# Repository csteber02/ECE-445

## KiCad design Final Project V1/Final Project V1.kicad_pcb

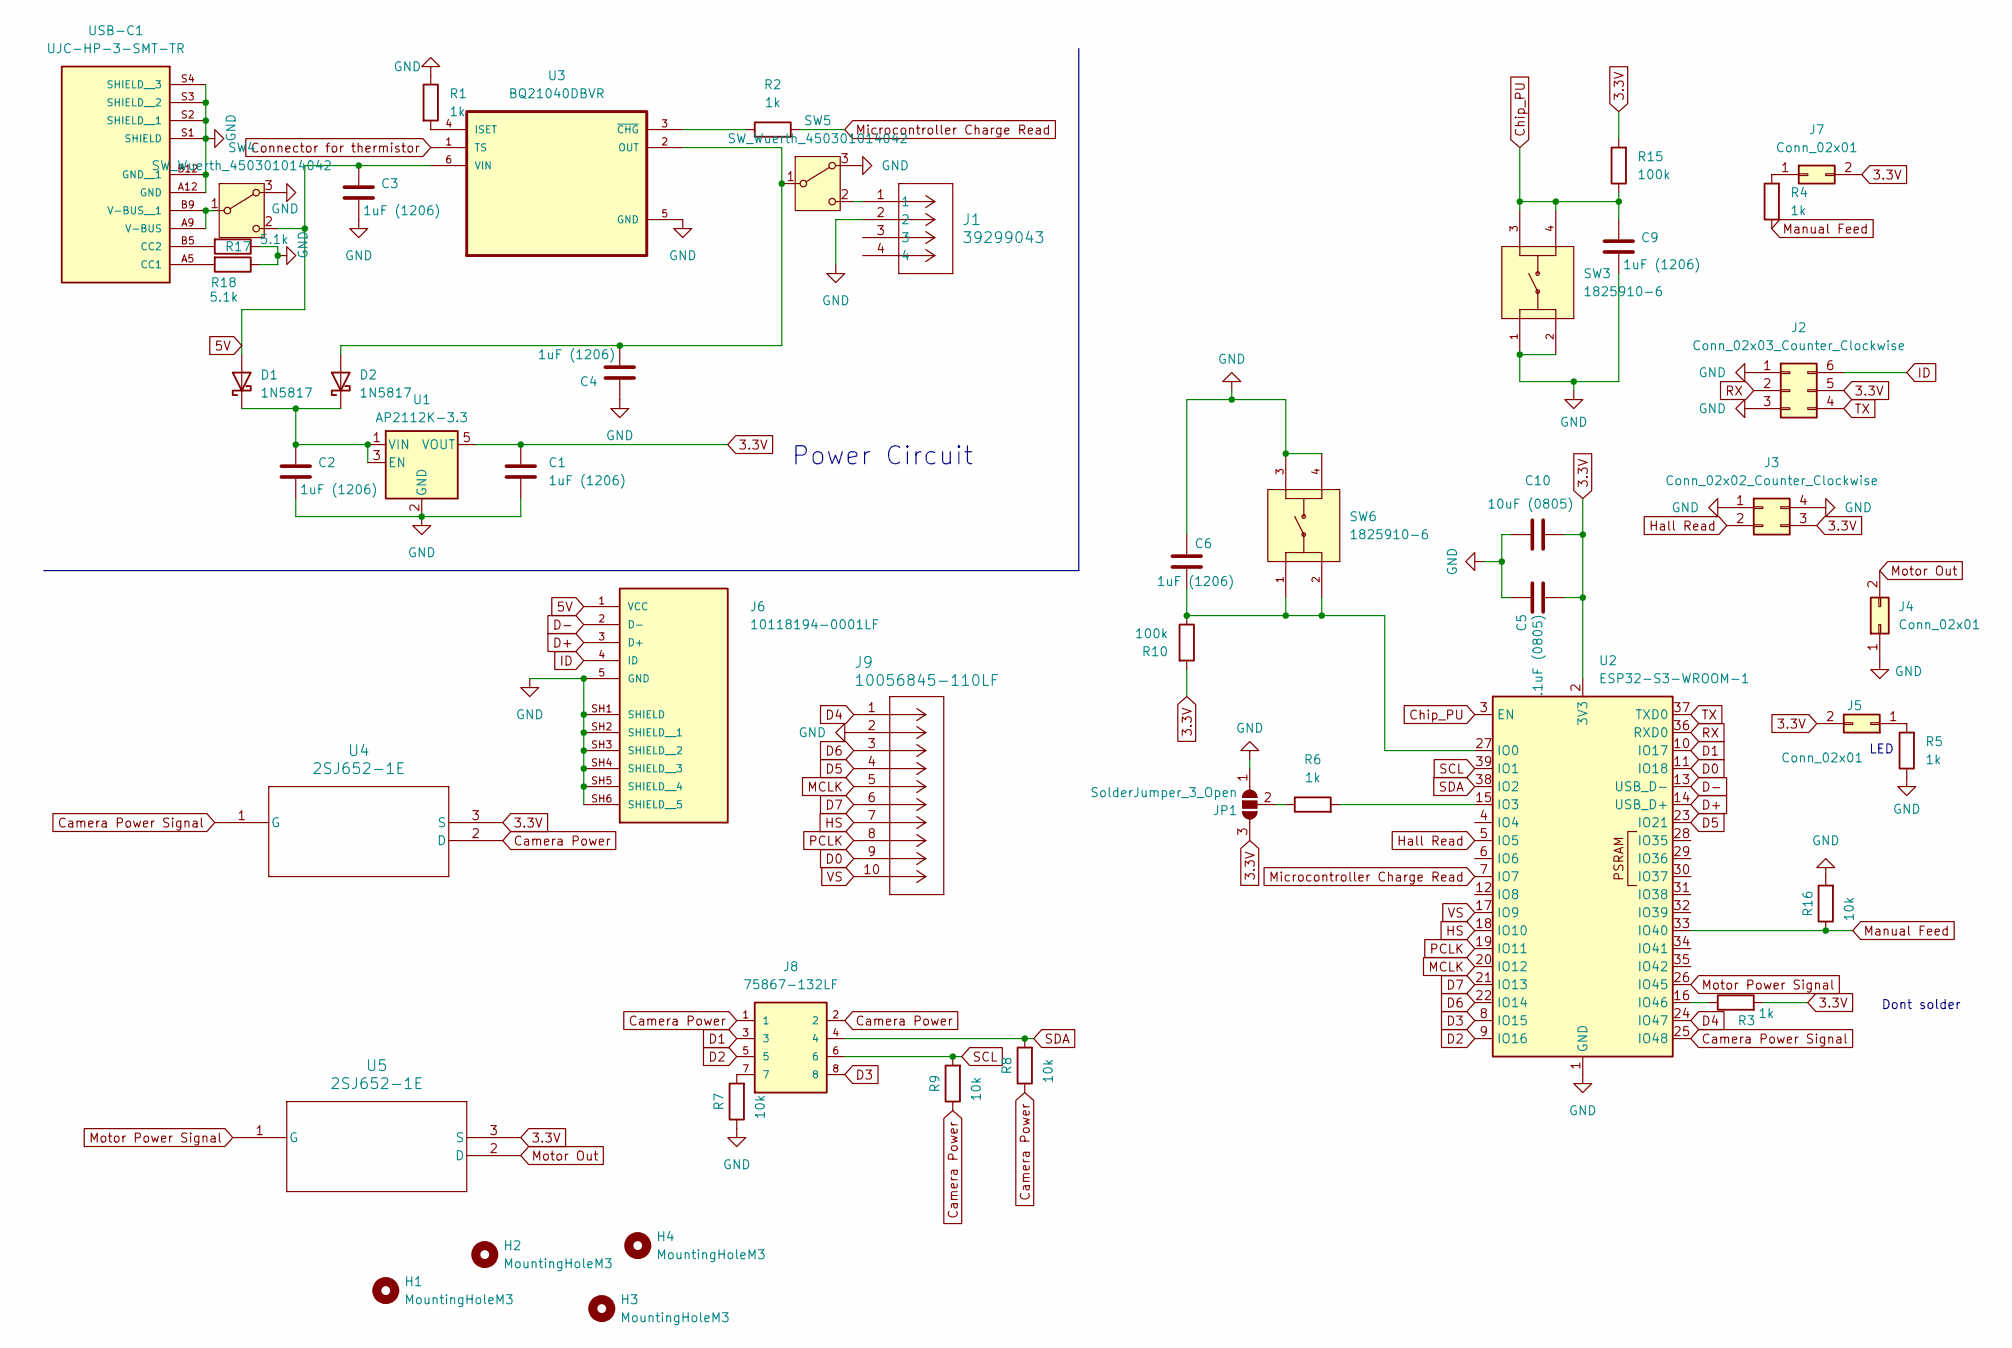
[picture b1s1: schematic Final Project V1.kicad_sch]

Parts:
C1, C2, C3, C4, C6, C9: 1uF (1206); C_1206_3216Metric_Pad1.33x1.80mm_HandSolder
C5: .1uF (0805); C_0805_2012Metric_Pad1.18x1.45mm_HandSolder
C10: 10uF (0805); C_0805_2012Metric_Pad1.18x1.45mm_HandSolder
D1, D2: 1N5817; D_DO-41_SOD81_P10.16mm_Horizontal
H1, H2, H3, H4: MountingHoleM3; MountingHole_3.2mm_M3_DIN965
J1: 39299043; CONN_5566-04x2_MOL
J2: Conn_02x03_Counter_Clockwise; PinHeader_2x03_P2.54mm_Vertical
J3: Conn_02x02_Counter_Clockwise; PinHeader_2x02_P2.54mm_Vertical
J4, J5, J7: Conn_02x01; PinHeader_2x01_P2.54mm_Vertical
J6: 10118194-0001LF; AMPHENOL_10118194-0001LF; PARTREV D
J8: 75867-132LF; HDRRA8W62P254_4X2_1737X957H920; MPN 75867-132LF
J9: 10056845-110LF; CON10_2X5_R2_FCI_GLE
JP1: SolderJumper_3_Open; SolderJumper-3_P2.0mm_Open_TrianglePad1.0x1.5mm
R1, R2, R3, R4, R5, R6: 1k; R_0805_2012Metric_Pad1.20x1.40mm_HandSolder
R7, R8, R9, R16: 10k; R_0805_2012Metric_Pad1.20x1.40mm_HandSolder
R10, R15: 100k; R_0805_2012Metric_Pad1.20x1.40mm_HandSolder
R17, R18: 5.1k; R_0805_2012Metric_Pad1.20x1.40mm_HandSolder
SW3, SW6: 1825910-6; SW_1825910-6-4; PARTREV C10
SW4, SW5: SW_Wuerth_450301014042; SW_Slide-03_Wuerth-WS-SLTV_10x2.5x6.4_P2.54mm
U1: AP2112K-3.3; SOT-23-5
U2: ESP32-S3-WROOM-1
U3: BQ21040DBVR; SOT95P280X145-6N
U4, U5: 2SJ652-1E; TO-220F-3SG_15P87X10P16_ONS
USB-C1: UJC-HP-3-SMT-TR; CUI_UJC-HP-3-SMT-TR; PARTREV 04/30/2020

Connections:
3.3V: C1.1, C5.2, C10.2, J2.5, J3.3, J5.2, J7.2, JP1.3 (B), R3.2, R10.2, R15.2, U1.5 (VOUT), U2.2 (3V3), U4.3 (S), U5.3 (S)
5V: C3.1, D1.2 (A), J6.1 (VCC), SW4.2 (C), U3.6 (VIN)
Camera Power: J8.1, J8.2, R8.1, R9.1, U4.2 (D)
Camera Power Signal: U2.25 (IO48), U4.1 (G)
Chip_PU: C9.1, R15.1, SW3.3, SW3.4, U2.3 (EN)
Connector for thermistor: U3.1 (TS)
D0: J9.9, U2.11 (IO18)
D1: J8.3, U2.10 (IO17)
D2: J8.5, U2.9 (IO16)
D3: J8.8, U2.8 (IO15)
D4: J9.1, U2.24 (IO47)
D5: J9.4, U2.23 (IO21)
D6: J9.3, U2.22 (IO14)
D7: J9.6, U2.21 (IO13)
D+: J6.3 (D+), U2.14 (USB_D+)
D-: J6.2 (D-), U2.13 (USB_D-)
GND: C1.2, C2.2, C3.2, C4.1, C5.1, C6.1, C9.2, C10.1, J1.2, J2.1, J2.3, J3.1, J3.4, J4.1, J6.5 (GND), J6.SH1 (SHIELD), J6.SH2 (SHIELD__1), J6.SH3 (SHIELD__2), J6.SH4 (SHIELD__3), J6.SH5 (SHIELD__4), J6.SH6 (SHIELD__5), J9.2, JP1.1 (A), R1.1, R5.1, R7.1, R16.2, R17.1, R18.1, SW3.1, SW3.2, SW4.3 (A), SW5.3 (A), SW6.3, SW6.4, U1.2 (GND), U2.1 (GND), U2.40 (GND), U2.41 (GND), U3.5 (GND), USB-C1.A12 (GND), USB-C1.B12 (GND__1), USB-C1.S1 (SHIELD), USB-C1.S2 (SHIELD__1), USB-C1.S3 (SHIELD__2), USB-C1.S4 (SHIELD__3)
HS: J9.7, U2.18 (IO10)
Hall Read: J3.2, U2.5 (IO5)
ID: J2.6, J6.4 (ID)
MCLK: J9.5, U2.20 (IO12)
Manual Feed: R4.1, R16.1, U2.33 (IO40)
Microcontroller Charge Read: R2.2, U2.7 (IO7)
Motor Out: J4.2, U5.2 (D)
Motor Power Signal: U2.26 (IO45), U5.1 (G)
unnamed: C2.1, D1.1 (K), D2.1 (K), U1.1 (VIN), U1.3 (EN)
unnamed: C4.2, D2.2 (A), SW5.1 (B), U3.2 (OUT)
unnamed: J5.1, R5.2
unnamed: J7.1, R4.2
unnamed: J8.7, R7.2
unnamed: JP1.2 (C), R6.1
unnamed: SW4.1 (B), USB-C1.A9 (V-BUS), USB-C1.B9 (V-BUS__1)
unnamed: J1.1, SW5.2 (C)
unnamed: C6.2, R10.1, SW6.1, SW6.2, U2.27 (IO0)
unnamed: R6.2, U2.15 (IO3)
unnamed: R3.1, U2.16 (IO46)
unnamed: R1.2, U3.4 (ISET)
unnamed: R2.1, U3.3 (~CHG)
unnamed: R18.2, USB-C1.A5 (CC1)
unnamed: R17.2, USB-C1.B5 (CC2)
PCLK: J9.8, U2.19 (IO11)
RX: J2.2, U2.36 (RXD0)
SCL: J8.6, R9.2, U2.39 (IO1)
SDA: J8.4, R8.2, U2.38 (IO2)
TX: J2.4, U2.37 (TXD0)
VS: J9.10, U2.17 (IO9)

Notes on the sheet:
Dont solder
LED
Power Circuit

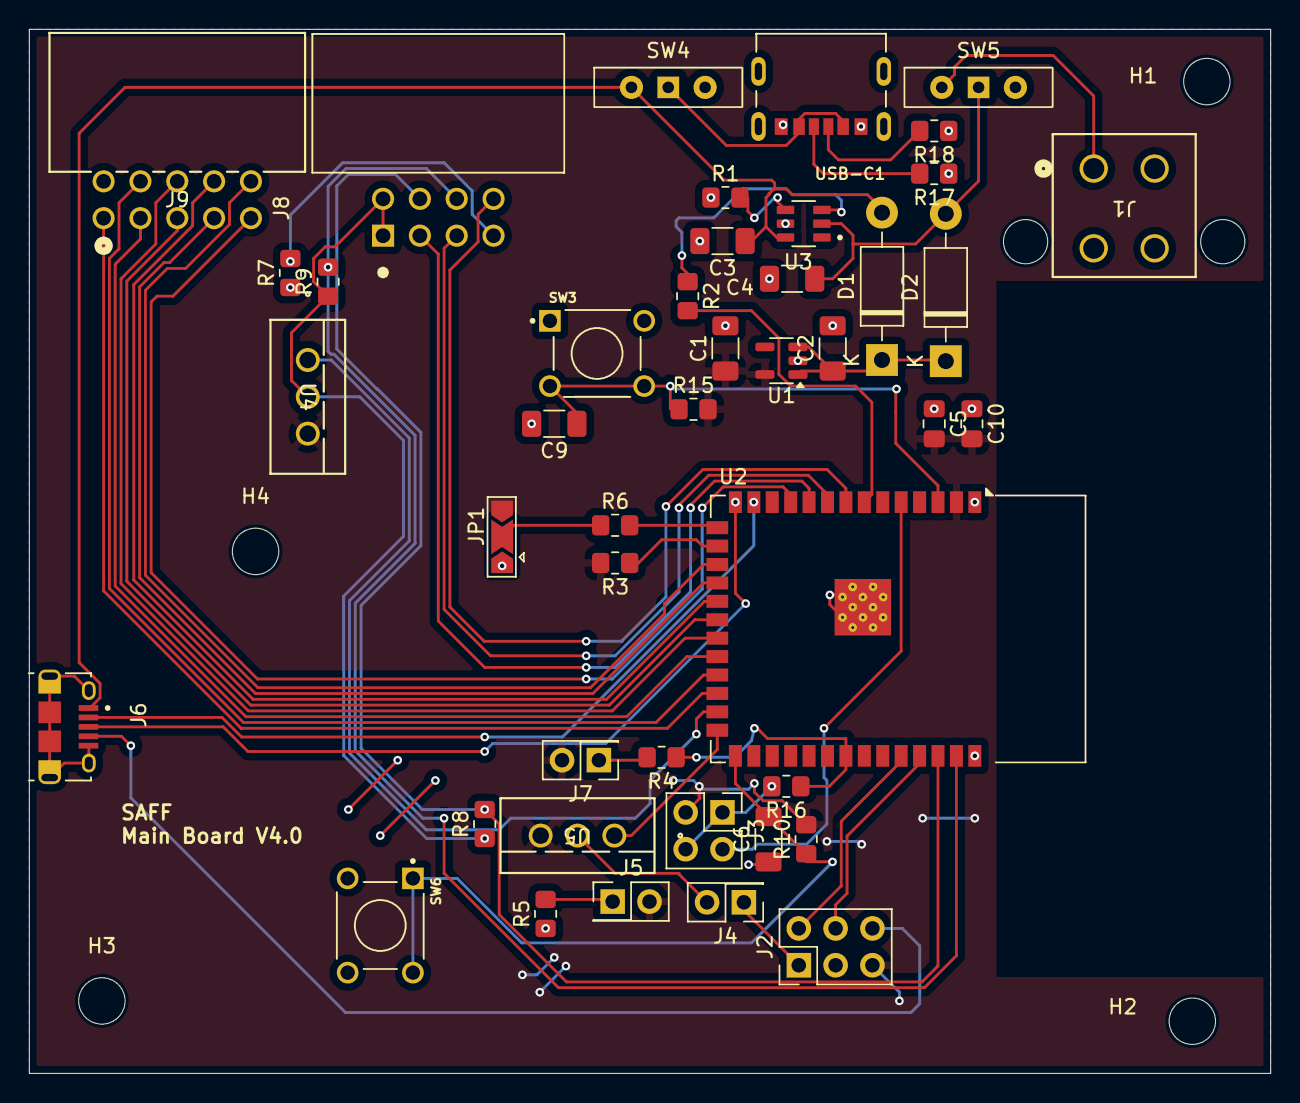
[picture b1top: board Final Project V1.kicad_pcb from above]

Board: 2 copper layers, 85.6 x 72.0 mm, 48 parts (0 on the bottom side), 45 nets.

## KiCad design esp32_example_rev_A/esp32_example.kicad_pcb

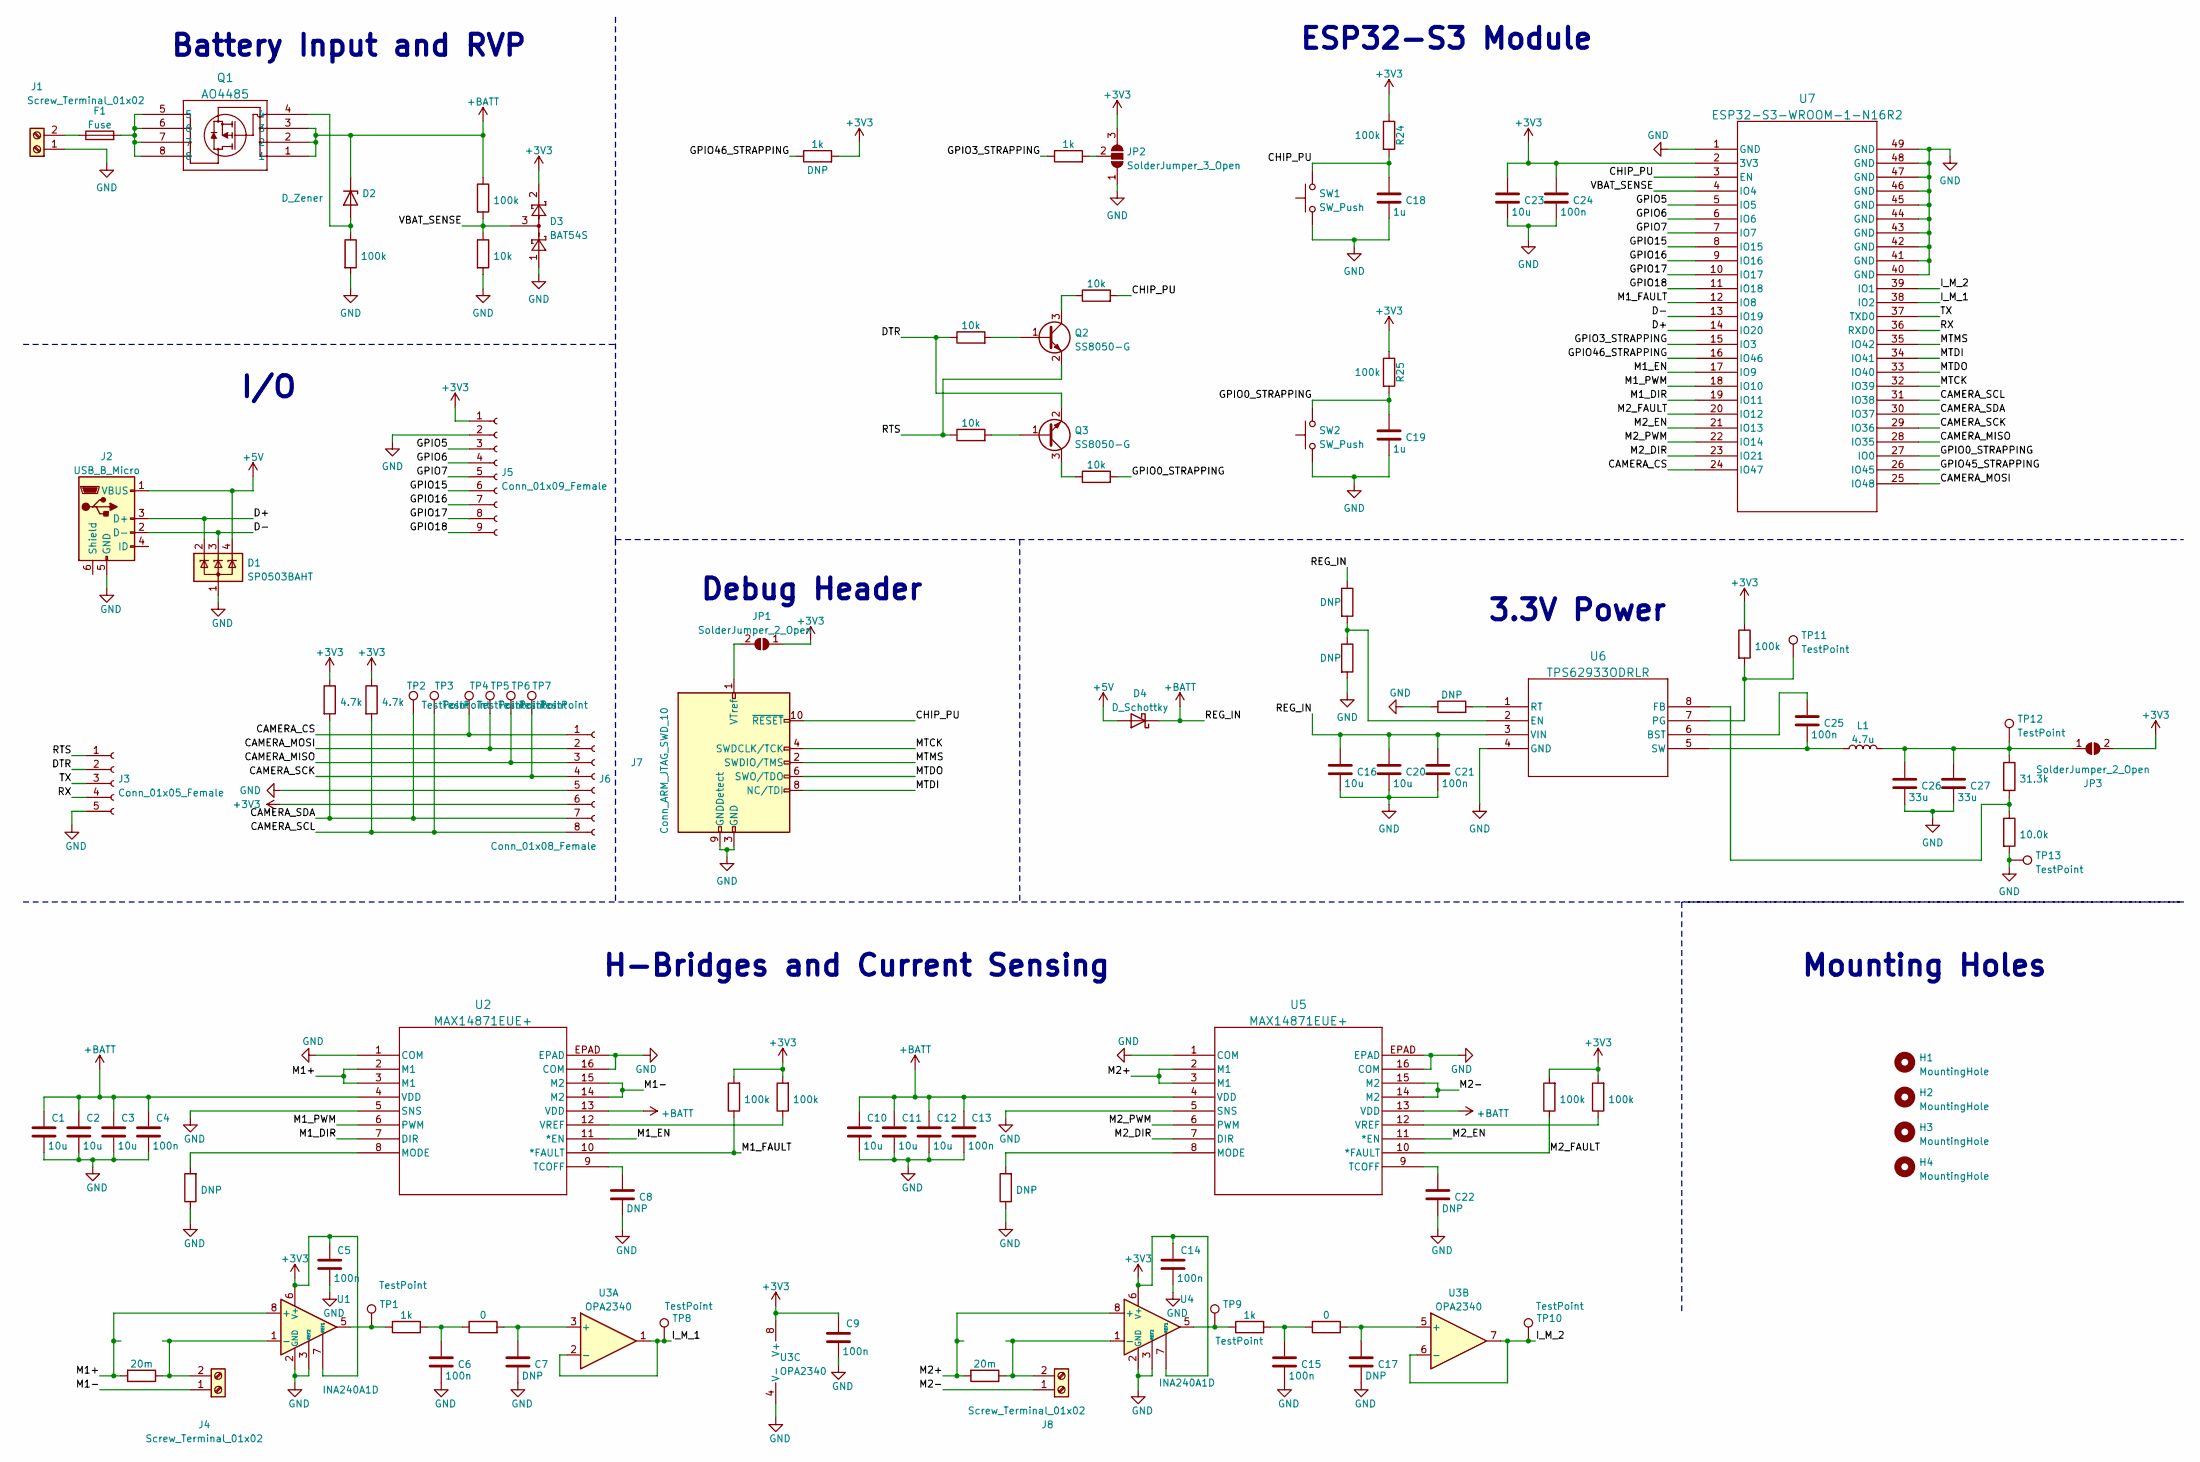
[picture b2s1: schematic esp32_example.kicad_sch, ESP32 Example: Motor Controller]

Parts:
C1, C2, C3, C10, C11, C12: 10u; R_1206_3216Metric
C4, C5, C6, C9, C13, C14, C15, C21, C24, C25: 100n; C_0805_2012Metric
C7, C8, C17, C22: DNP; C_0805_2012Metric
C16, C20, C23: 10u; C_0805_2012Metric
C18, C19: 1u; C_0805_2012Metric
C26, C27: 33u; C_0805_2012Metric
D1: SP0503BAHT; SOT-143
D2: D_Zener; SOD-123_ONS
D3: BAT54S; SOT-23
D4: D_Schottky; D_SMA
F1: Fuse; Fuseholder_Littelfuse_Nano2_154x
H1, H2, H3, H4: MountingHole; MountingHole_3.2mm_M3
J1, J4, J8: Screw_Terminal_01x02; TerminalBlock_Phoenix_MKDS-1,5-2-5.08_1x02_P5.08mm_Horizont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
J2: USB_B_Micro; USB_Micro-B_Amphenol_10118194_Horizontal
J3: Conn_01x05_Female; PinHeader_1x05_P2.54mm_Vertical
J5: Conn_01x09_Female; PinHeader_1x09_P2.54mm_Vertical
J6: Conn_01x08_Female; PinHeader_1x08_P2.54mm_Vertical
J7: Conn_ARM_JTAG_SWD_10; IDC-Header_2x05_P2.54mm_Vertical
JP1, JP3: SolderJumper_2_Open; SolderJumper-2_P1.3mm_Open_TrianglePad1.0x1.5mm
JP2: SolderJumper_3_Open; SolderJumper-3_P2.0mm_Open_TrianglePad1.0x1.5mm
L1: 4.7u; L_Taiyo-Yuden_NR-60xx
Q1: AO4485; SO8SOP-8L_AOS
Q2, Q3: SS8050-G; SOT-23
R1, R15: 20m; R_1206_3216Metric
R2, R16, R22, R23, R26: DNP; R_0805_2012Metric
R3, R4: 4.7k; R_0805_2012Metric
R5, R12, R17, R20: 1k; R_0805_2012Metric
R6, R8, R10, R11, R24, R25, R27, R28, R29: 100k; R_0805_2012Metric
R7, R21: 0; R_0805_2012Metric
R9, R13, R14, R18, R19: 10k; R_0805_2012Metric
R30: 31.3k; R_0805_2012Metric
R31: 10.0k; R_0805_2012Metric
SW1, SW2: SW_Push; SW_SPST_B3S-1000
TP1, TP2, TP3, TP4, TP5, TP6, TP7, TP8, TP9, TP10, TP12, TP13: TestPoint; TestPoint_Keystone_5010-5014_Multipurpose
TP11: TestPoint; TestPoint_Pad_D2.0mm
U1, U4: INA240A1D; SOIC-8_3.9x4.9mm_P1.27mm
U2, U5: MAX14871EUE+; 21-0108_U16E&plus_3_MXM
U3: OPA2340; SOIC-8_3.9x4.9mm_P1.27mm
U6: TPS62933ODRLR; SOT5X3-8_DRL_TEX
U7: ESP32-S3-WROOM-1-N16R2; ESP32-S3-WROOM-1_EXP

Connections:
+3V3: C5.1, C9.1, C14.1, C23.1, C24.1, D3.2, J5.1, J6.6, JP1.1 (A), JP2.3 (B), JP3.2 (B), R3.1, R4.1, R10.2, R11.2, R12.2, R24.1, R25.1, R27.2, R28.2, R29.1, U1.6 (V+), U1.7 (REF1), U3.8 (V+), U4.6 (V+), U4.7 (REF1), U7.2 (3V3)
+5V: D1.4 (K), D4.2 (A), J2.1 (VBUS)
+BATT: C1.1, C2.1, C3.1, C4.1, C10.1, C11.1, C12.1, C13.1, C16.1, C20.1, C21.1, D2.1 (K), D4.1 (K), Q1.1, Q1.2, Q1.3, R8.1, R22.1, U2.4 (VDD), U2.13 (VDD), U5.4 (VDD), U5.13 (VDD), U6.3 (VIN)
/CAMERA_CS: J6.1, TP4.1, U7.24 (IO47)
/CAMERA_MISO: J6.3, TP6.1, U7.28 (IO35)
/CAMERA_MOSI: J6.2, TP5.1, U7.25 (IO48)
/CAMERA_SCK: J6.4, TP7.1, U7.29 (IO36)
/CAMERA_SCL: J6.8, R4.2, TP3.1, U7.31 (IO38)
/CAMERA_SDA: J6.7, R3.2, TP2.1, U7.30 (IO37)
/CHIP_PU: C18.1, J7.10 (~RESET), R18.2, R24.2, SW1.2, U7.3 (EN)
/D+: D1.2 (K), J2.3 (D+), U7.14 (IO20)
/D-: D1.3 (K), J2.2 (D-), U7.13 (IO19)
/DTR: J3.2, Q3.2 (E), R13.1
/GPIO0_STRAPPING: C19.1, R19.2, R25.2, SW2.2, U7.27 (IO0)
/GPIO3_STRAPPING: R17.1, U7.15 (IO3)
/GPIO5: J5.3, U7.5 (IO5)
/GPIO6: J5.4, U7.6 (IO6)
/GPIO7: J5.5, U7.7 (IO7)
/GPIO15: J5.6, U7.8 (IO15)
/GPIO16: J5.7, U7.9 (IO16)
/GPIO17: J5.8, U7.10 (IO17)
/GPIO18: J5.9, U7.11 (IO18)
/GPIO45_STRAPPING: U7.26 (IO45)
/GPIO46_STRAPPING: R12.1, U7.16 (IO46)
/I_M_1: TP8.1, U3.1, U3.2 (-), U7.38 (IO2)
/I_M_2: TP10.1, U3.6 (-), U3.7, U7.39 (IO1)
/M1+: R1.2, U1.8 (+), U2.2 (M1), U2.3 (M1)
/M1-: J4.1, U2.14 (M2), U2.15 (M2)
/M1_DIR: U2.7 (DIR), U7.19 (IO11)
/M1_EN: U2.11 (*EN), U7.17 (IO9)
/M1_FAULT: R10.1, U2.10 (*FAULT), U7.12 (IO8)
/M1_PWM: U2.6 (PWM), U7.18 (IO10)
/M2+: R15.2, U4.8 (+), U5.2 (M1), U5.3 (M1)
/M2-: J8.1, U5.14 (M2), U5.15 (M2)
/M2_DIR: U5.7 (DIR), U7.23 (IO21)
/M2_EN: U5.11 (*EN), U7.21 (IO13)
/M2_FAULT: R27.1, U5.10 (*FAULT), U7.20 (IO12)
/M2_PWM: U5.6 (PWM), U7.22 (IO14)
/MTCK: J7.4 (SWDCLK/TCK), U7.32 (IO39)
/MTDI: J7.8 (NC/TDI), U7.34 (IO41)
/MTDO: J7.6 (SWO/TDO), U7.33 (IO40)
/MTMS: J7.2 (SWDIO/TMS), U7.35 (IO42)
/RTS: J3.1, Q2.2 (E), R14.1
/RX: J3.4, U7.36 (RXD0)
/TX: J3.3, U7.37 (TXD0)
/VBAT_SENSE: D3.3, R8.2, R9.1, U7.4 (IO4)
GND: C1.2, C2.2, C3.2, C4.2, C5.2, C6.2, C7.2, C8.2, C9.2, C10.2, C11.2, C12.2, C13.2, C14.2, C15.2, C16.2, C17.2, C18.2, C19.2, C20.2, C21.2, C22.2, C23.2, C24.2, C26.2, C27.2, D1.1 (A), D3.1, J1.1, J2.5 (GND), J3.5, J5.2, J6.5, J7.3 (GND), J7.5 (GND), J7.9 (GNDDetect), JP2.1 (A), R2.1, R6.2, R9.2, R16.1, R23.2, R26.1, R31.2, SW1.1, SW2.1, TP13.1, U1.2 (GND), U1.3 (REF2), U1.4 (GND), U2.1 (COM), U2.5 (SNS), U2.16 (COM), U2.EPAD, U3.4 (V-), U4.2 (GND), U4.3 (REF2), U4.4 (GND), U5.1 (COM), U5.5 (SNS), U5.16 (COM), U5.EPAD, U6.4 (GND), U7.1 (GND), U7.40 (GND), U7.41 (GND), U7.42 (GND), U7.43 (GND), U7.44 (GND), U7.45 (GND), U7.46 (GND), U7.47 (GND), U7.48 (GND), U7.49 (GND)
unnamed: C6.1, R5.2, R7.1
unnamed: C7.1, R7.2, U3.3 (+)
unnamed: C8.1, U2.9 (TCOFF)
unnamed: C15.1, R20.2, R21.1
unnamed: C17.1, R21.2, U3.5 (+)
unnamed: C22.1, U5.9 (TCOFF)
unnamed: C25.1, U6.6 (BST)
unnamed: C25.2, L1.1, U6.5 (SW)
unnamed: C26.1, C27.1, JP3.1 (A), L1.2, R30.1, TP12.1
unnamed: D2.2 (A), Q1.4, R6.1
unnamed: F1.1, J1.2
unnamed: F1.2, Q1.5, Q1.6, Q1.7, Q1.8
unnamed: J4.2, R1.1, U1.1 (-)
unnamed: J7.1 (VTref), JP1.2 (B)
unnamed: J8.2, R15.1, U4.1 (-)
unnamed: JP2.2 (C), R17.2
unnamed: Q2.1 (B), R13.2
unnamed: Q2.3 (C), R18.1
unnamed: Q3.1 (B), R14.2
unnamed: Q3.3 (C), R19.1
unnamed: R2.2, U2.8 (MODE)
unnamed: R5.1, TP1.1, U1.5
unnamed: R11.1, U2.12 (VREF)
unnamed: R16.2, U5.8 (MODE)
unnamed: R20.1, TP9.1, U4.5
unnamed: R22.2, R23.1, U6.2 (EN)
unnamed: R26.2, U6.1 (RT)
unnamed: R28.1, U5.12 (VREF)
unnamed: R29.2, TP11.1, U6.7 (PG)
unnamed: R30.2, R31.1, U6.8 (FB)

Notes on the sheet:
H-Bridges and Current Sensing
ESP32-S3 Module
Debug Header
Mounting Holes
3.3V Power
Battery Input and RVP
I/O

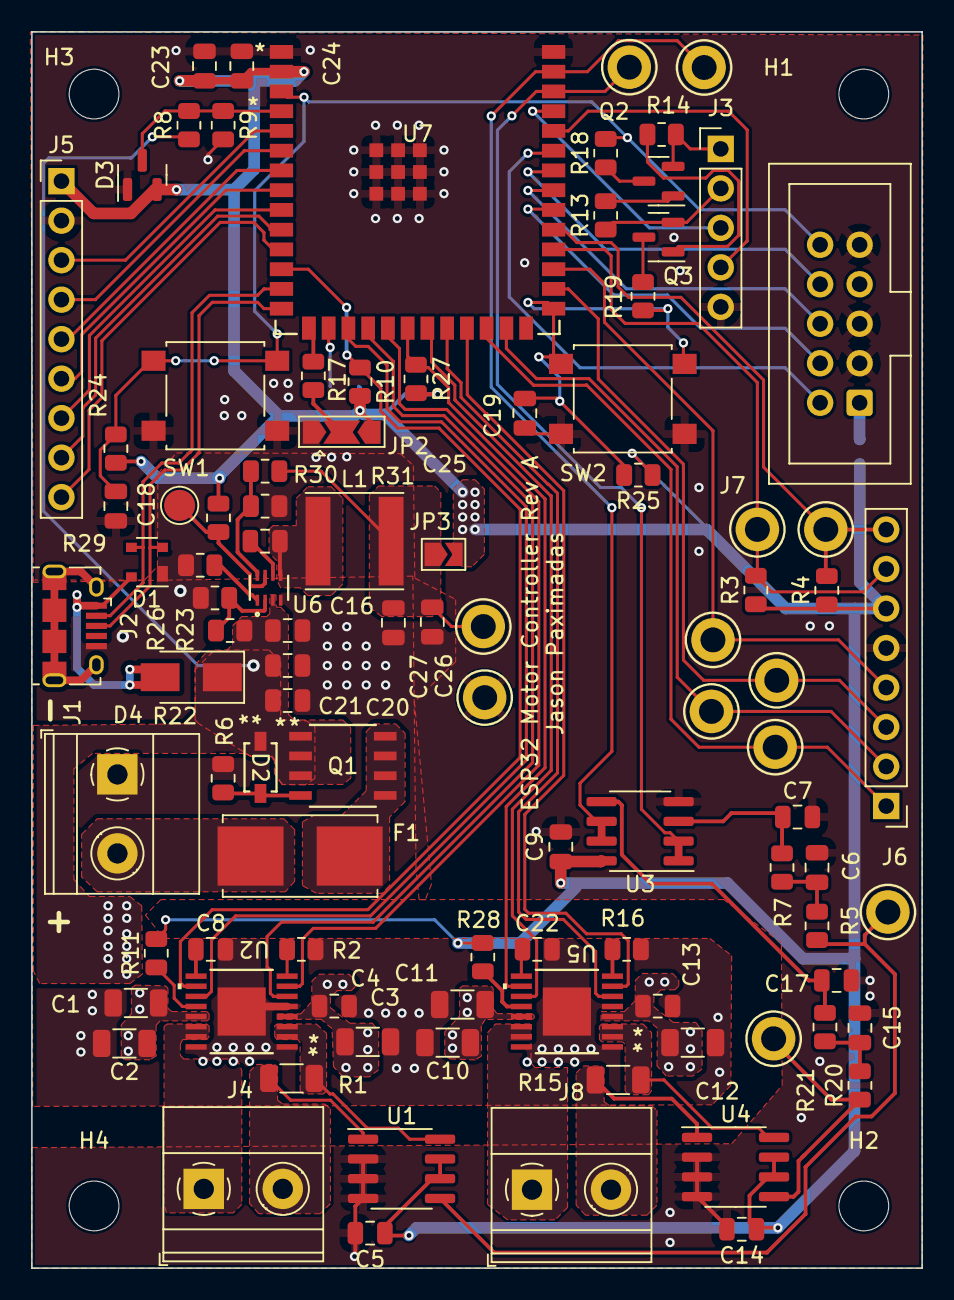
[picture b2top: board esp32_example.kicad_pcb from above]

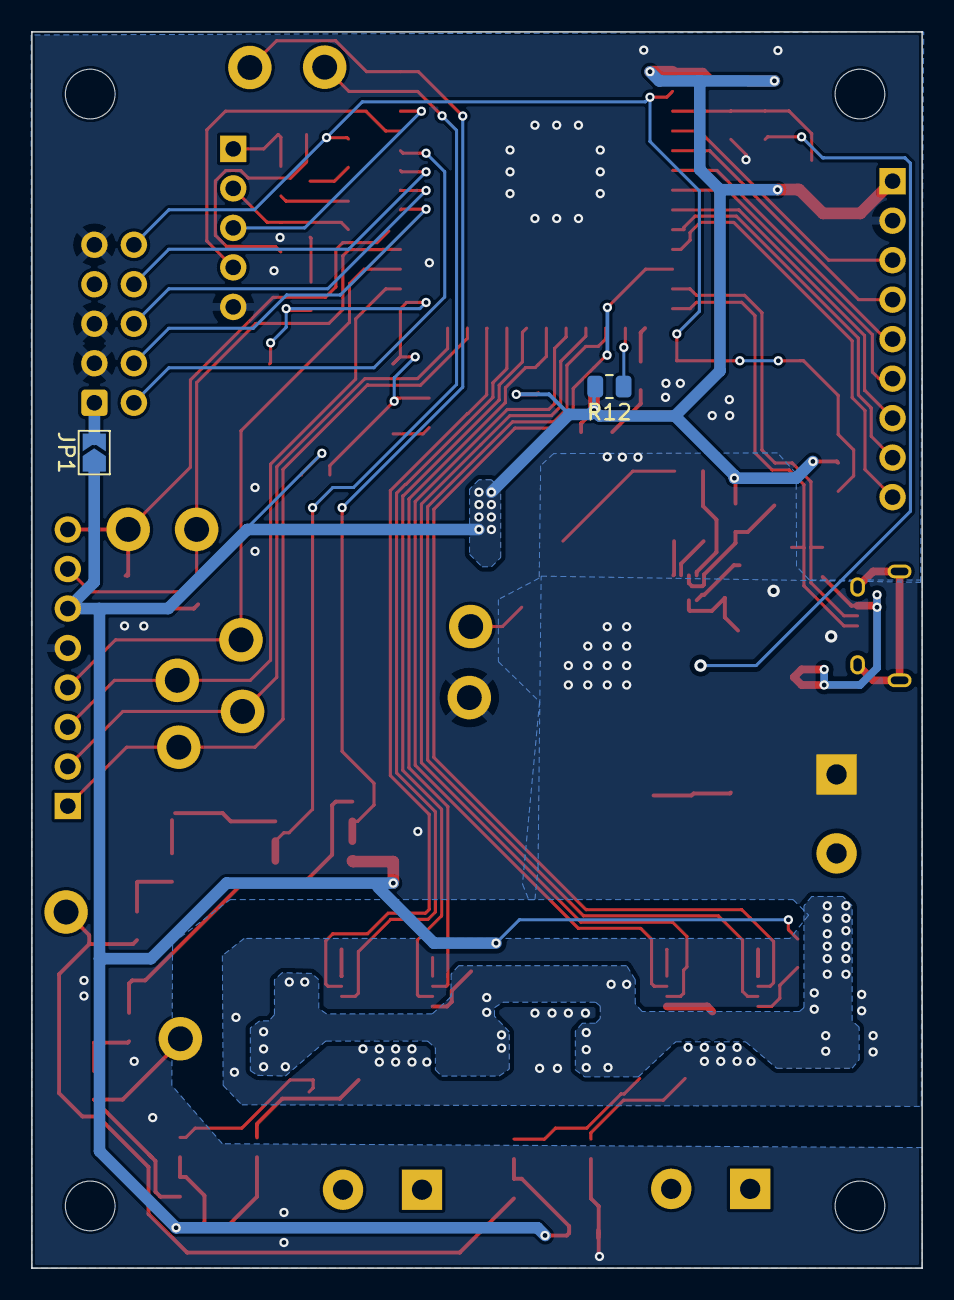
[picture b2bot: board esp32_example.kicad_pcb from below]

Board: 2 copper layers, 57.2 x 79.5 mm, 104 parts (2 on the bottom side), 76 nets.

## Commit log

2025-02-24 Original File Push
2025-02-27 Finish power rail
2025-02-27 Worked on PCB
2025-03-04 Finish V1 Board
2025-03-10 Change socket headers to pins and use through-hole buttons. Need to try switch on pcb when arrives and change camera connector
2025-03-28 V2 Board
2025-03-30 Added resistors to control channel on USB-C cause I am a silly goose and didn't do that before
2025-04-11 V4 Schematic. Will work with V3
2025-05-04 Upload Notebooks
2025-05-06 Upload Colby Notebook
2025-05-07 Upload Jeremy Notebook
